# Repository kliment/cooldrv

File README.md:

Motor driver using DRV8825, originally designed in Eagle, now converted to KiCAD format.

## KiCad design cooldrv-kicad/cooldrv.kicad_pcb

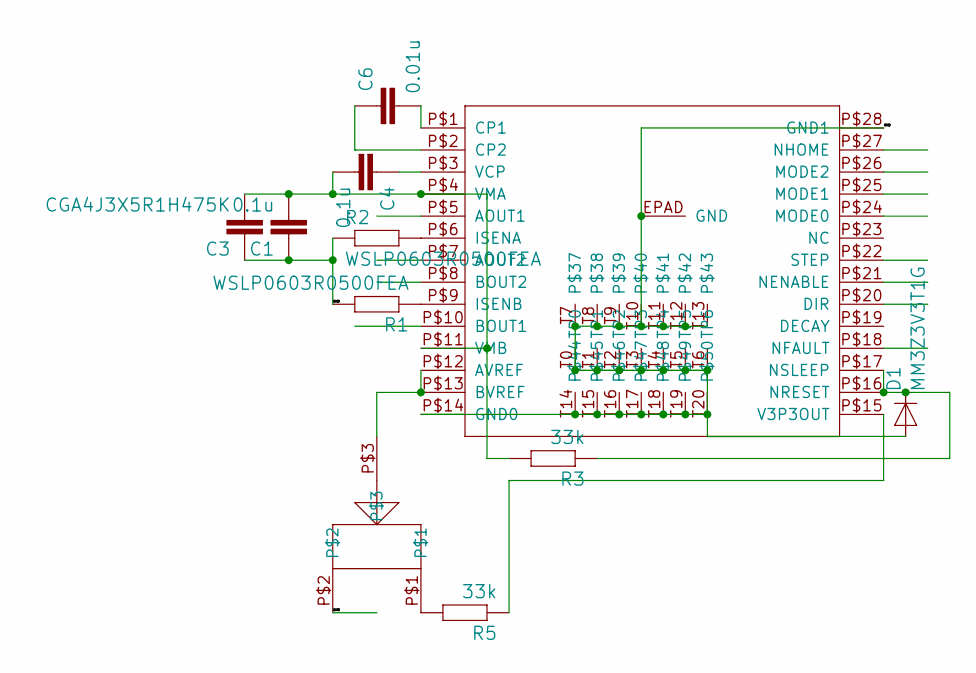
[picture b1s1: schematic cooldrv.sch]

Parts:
C1: 0.1u; C0603
C3: CGA4J3X5R1H475K; C0805K
C4: 0.1u; C0603K
C6: 0.01u; C0603
D1: MM3Z3V3T1G; SOD323-R
R1, R2: WSLP0603R0500FEA; 0805C
R3, R5: 33k; R0603
U$1: DRV8825; ETSSOP28
U$2: EVM-3YSX50B14; TRIMMER3MM

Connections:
/GND: C1.1, C3.1, D1.A, R1.2, R2.1, U$1.EPAD (GND), U$1.P$14 (GND0), U$1.P$28 (GND1), U$1.T0 (TP0), U$1.T1 (TP1), U$1.T2 (TP2), U$1.T3 (TP3), U$1.T4 (TP4), U$1.T5 (TP5), U$1.T6 (TP6), U$1.T7, U$1.T8, U$1.T9, U$1.T10, U$1.T11, U$1.T12, U$1.T13, U$1.T14, U$1.T15, U$1.T16, U$1.T17, U$1.T18, U$1.T19, U$1.T20, U$2.P$2
unnamed: C1.2, C3.2, C4.2, R3.2, U$1.P$4 (VMA), U$1.P$11 (VMB)
unnamed: C4.1, U$1.P$3 (VCP)
unnamed: C6.1, U$1.P$2 (CP2)
unnamed: C6.2, U$1.P$1 (CP1)
unnamed: D1.C, R3.1, U$1.P$16 (NRESET), U$1.P$17 (NSLEEP)
unnamed: R1.1, U$1.P$9 (ISENB)
unnamed: R2.2, U$1.P$6 (ISENA)
unnamed: R5.1, U$1.P$15 (V3P3OUT)
unnamed: R5.2, U$2.P$1
unnamed: U$1.P$12 (AVREF), U$1.P$13 (BVREF), U$2.P$3

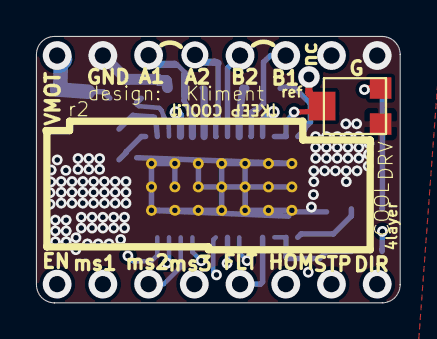
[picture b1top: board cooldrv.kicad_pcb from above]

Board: 4 copper layers, 20.2 x 14.8 mm, 11 parts (0 on the bottom side), 11 nets.

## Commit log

2020-09-14 Move Eagle files into separate directory
2020-09-14 Convert to Kicad format and re-generate production files and images
2020-09-14 Add README
